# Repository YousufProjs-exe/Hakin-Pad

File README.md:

## Hakin Pad™
[**README & the WHOLE build is indeed whole done by me(Yousuf) only and the AI used is as per regulations are mentioned in the project description.**]
A small custom macropad designed from scratch with KiCad.

--
Hakin Pad™
Designed on a screen.
Built on a desk.
A few commands.
A lot of buttons. And
Some productive copper too.
--

# Hakin Pad™

 Designed on a screen.  
 Built on a desk.

Hakin Pad™ is my second hardware project and my first custom macropad, designed from scratch in KiCad.

It features a XIAO RP2040, physical keys, two rotary encoders, a 0.91" I2C OLED, a custom PCB, and a custom 3D-printed case.

## Features

- XIAO RP2040
- 7 physical keys
- 2 rotary encoders with push switches
- 0.91" I2C OLED display
- Custom PCB designed in KiCad
- Custom 3D-printed case
- Custom firmware

## Files

- `PCB/` — KiCad schematic, PCB and fabrication files
- `CAD/` — 3D case files
- `Firmware/` — firmware
- `production/` — production files
- `Screenshots/` — project images

## Tools

- KiCad
- FreeCAD
- CircuitPython / KMK
- Git & GitHub

## Status

**Design complete — ready for production.**

This project was designed and documented by me, Yousuf. AI assistance was used only where permitted by the project/program rules.

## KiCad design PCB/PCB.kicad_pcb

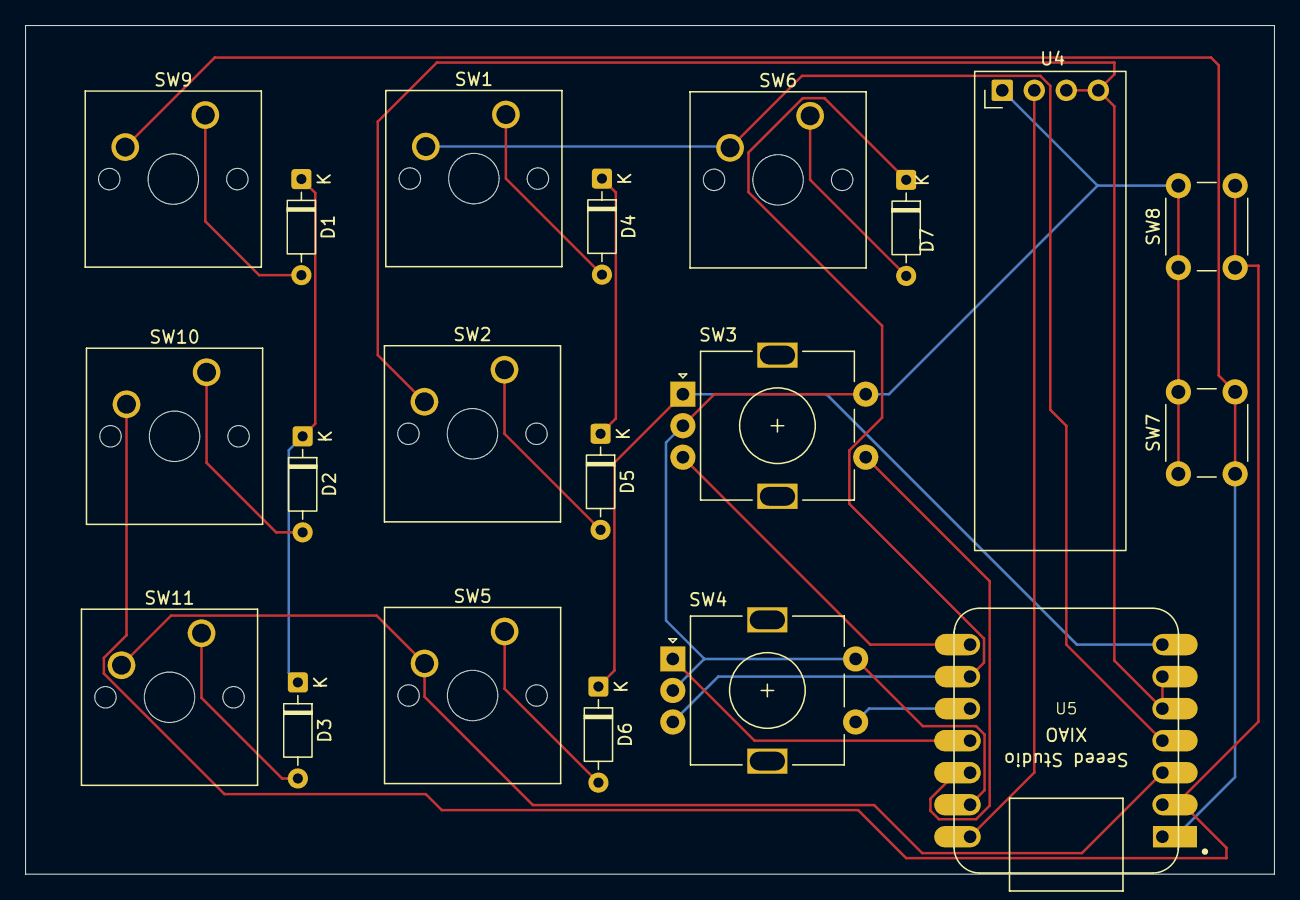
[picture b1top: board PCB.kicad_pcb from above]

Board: 2 copper layers, 99.1 x 67.3 mm, 20 parts (0 on the bottom side), 22 nets.

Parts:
D1, D2, D3, D4, D5, D6, D7: 1N4148; D_DO-35_SOD27_P7.62mm_Horizontal
SW1: SW4_Push; SW_Cherry_MX_1.00u_PCB
SW2: SW5_Push; SW_Cherry_MX_1.00u_PCB
SW3, SW4: RotaryEncoder_Switch; RotaryEncoder_Alps_EC11E-Switch_Vertical_H20mm
SW5: SW6_Push; SW_Cherry_MX_1.00u_PCB
SW6: SW7_Push; SW_Cherry_MX_1.00u_PCB
SW7: SW_Push-Mode0; SW_PUSH_6mm
SW8: SW_Push-Mode1; SW_PUSH_6mm
SW9: SW1_Push; SW_Cherry_MX_1.00u_PCB
SW10: SW2_Push; SW_Cherry_MX_1.00u_PCB
SW11: SW3_Push; SW_Cherry_MX_1.00u_PCB
U4: ER_OLEDM0.91_1x-I2C
U5: MOUDLE-SEEEDUINO-XIAO; XIAO-Generic-Hybrid-14P-2.54-21X17.8MM

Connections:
unnamed: D1.2 (A), SW9.1
unnamed: D1.1 (K), D2.1 (K), D3.1 (K)
unnamed: D2.2 (A), SW10.1
unnamed: D3.2 (A), SW11.1
unnamed: D4.2 (A), SW1.1
unnamed: D4.1 (K), D5.1 (K)
unnamed: D5.2 (A), SW2.1
unnamed: D6.2 (A), SW5.1
unnamed: D6.1 (K), SW3.A, U5.7 (PB08_A6_D6_TX)
unnamed: D7.2 (A), SW6.1
unnamed: D7.1 (K), SW4.B, U5.9 (PA7_A8_D8_SCK)
unnamed: SW3.C, SW3.S2, SW4.C, SW4.S2, SW7.1, SW8.1, U4.1 (GND), U5.13 (GND)
unnamed: SW2.2, U4.3 (SCL), U4.4 (SDA), U5.5 (PA8_A4_D4_SDA), U5.6 (PA9_A5_D5_SCL)
unnamed: U4.2 (VCC), U5.14 (5V)
unnamed: SW3.S1, U5.12 (3V3)
unnamed: SW7.2, SW9.2, U5.1 (PA02_A0_D0)
unnamed: SW8.2, SW10.2, U5.2 (PA4_A1_D1)
unnamed: SW4.S1, U5.10 (PA5_A9_D9_MISO)
unnamed: SW4.A, U5.11 (PA6_A10_D10_MOSI)
unnamed: SW5.2, SW11.2, U5.3 (PA10_A2_D2)
unnamed: SW1.2, SW6.2, U5.4 (PA11_A3_D3)
unnamed: SW3.B, U5.8 (PB09_A7_D7_RX)
